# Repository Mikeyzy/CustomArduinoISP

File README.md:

# CustomArduinoISP
Custom ArduinoISP Board with Voltage Selection

This is a custom designed ArduinoISP based AVR ISP board, with 5V/3V3 selection switch and pwoer dilivery switch, you need ArduinoISP software which is avaliable in Examples from Arduino IDE, you can download it from www.arduino.cc

you need Autodesk EAGLE to open the schematics.

the license only apply to the hardware design, since the software is not included.

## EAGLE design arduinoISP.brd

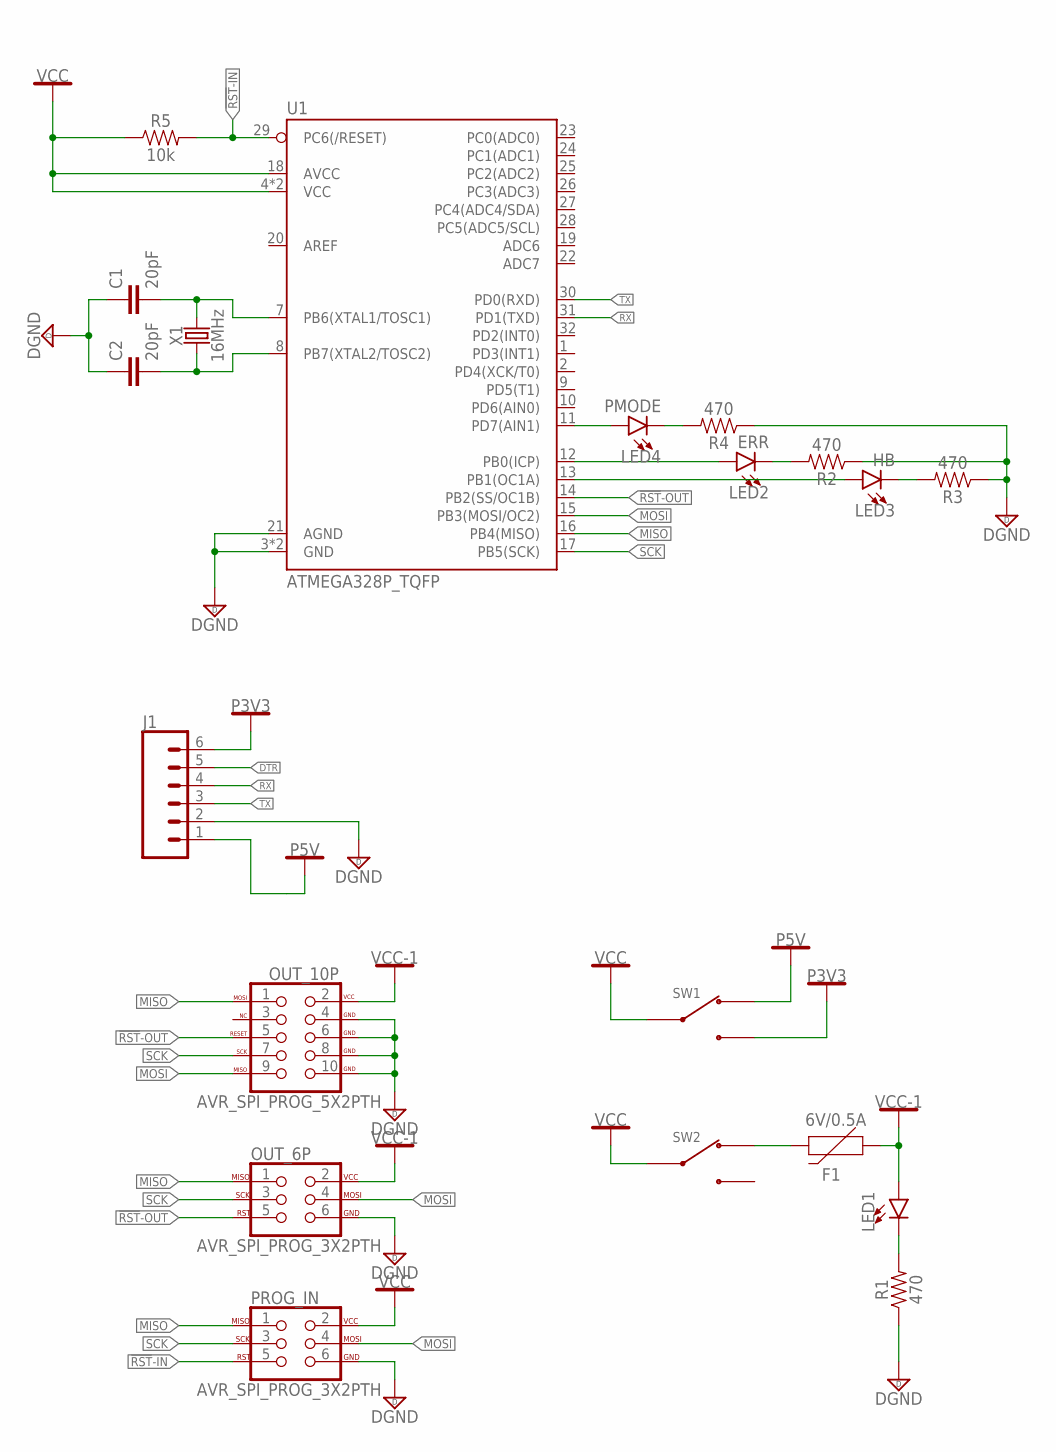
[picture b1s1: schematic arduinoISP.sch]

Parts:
C1, C2: 20pF; 0603
F1: 6V/0.5A; 1206
J1: CONN_06NO_SILK_NO_POP; 1X06_NO_SILK
LED1: LED3MM; LED_3MM
LED2: ERR; LED_3MM
LED3: HB; LED_3MM
LED4: PMODE; LED_3MM
OUT_6P: AVR_SPI_PROG_3X2PTH; 2X3
OUT_10P: AVR_SPI_PROG_5X2PTH; 2X5
PROG_IN: AVR_SPI_PROG_3X2PTH; 2X3
R1, R2, R3, R4: 470; 0603
R5: 10k; 0603
SW1, SW2: SW-SPDT_SS-12D02-VG4; SW_SS-12D10L5_FP
U1: ATMEGA328P_TQFP; TQFP32-08
X1: 16MHz; HC49US

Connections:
!RST!-IN: PROG_IN.5, R5.2, U1.29 (PC6(/RESET))
!RST!-OUT: OUT_6P.5, OUT_10P.5 (RESET), U1.14 (PB2(SS/OC1B))
DGND: C1.1, C2.1, J1.2, OUT_6P.6, OUT_10P.4 (GND), OUT_10P.6 (GND), OUT_10P.8 (GND), OUT_10P.10 (GND), PROG_IN.6, R1.1, R2.1, R3.1, R4.1, U1.3 (GND), U1.5 (GND), U1.21 (AGND)
DTR: J1.5
MISO: OUT_6P.1, OUT_10P.1 (MOSI), PROG_IN.1, U1.16 (PB4(MISO))
MOSI: OUT_6P.4, OUT_10P.9 (MISO), PROG_IN.4, U1.15 (PB3(MOSI/OC2))
unnamed: LED1.K (C), R1.2
unnamed: LED2.K (C), R2.2
unnamed: LED2.A, U1.12 (PB0(ICP))
unnamed: LED3.K (C), R3.2
unnamed: LED4.K (C), R4.2
unnamed: LED3.A, U1.13 (PB1(OC1A))
unnamed: LED4.A, U1.11 (PD7(AIN1))
unnamed: C1.2, U1.7 (PB6(XTAL1/TOSC1)), X1.2
unnamed: C2.2, U1.8 (PB7(XTAL2/TOSC2)), X1.1
unnamed: F1.2, SW2.P$1 (A)
P3V3: J1.6, SW1.P$3 (B)
P5V: J1.1, SW1.P$1 (A)
RX: J1.4, U1.31 (PD1(TXD))
SCK: OUT_6P.3, OUT_10P.7 (SCK), PROG_IN.3, U1.17 (PB5(SCK))
TX: J1.3, U1.30 (PD0(RXD))
VCC: PROG_IN.2, R5.1, SW1.P$2 (COM), SW2.P$2 (COM), U1.4 (VCC), U1.6 (VCC), U1.18 (AVCC)
VCC1: F1.1, LED1.A, OUT_6P.2, OUT_10P.2 (VCC)

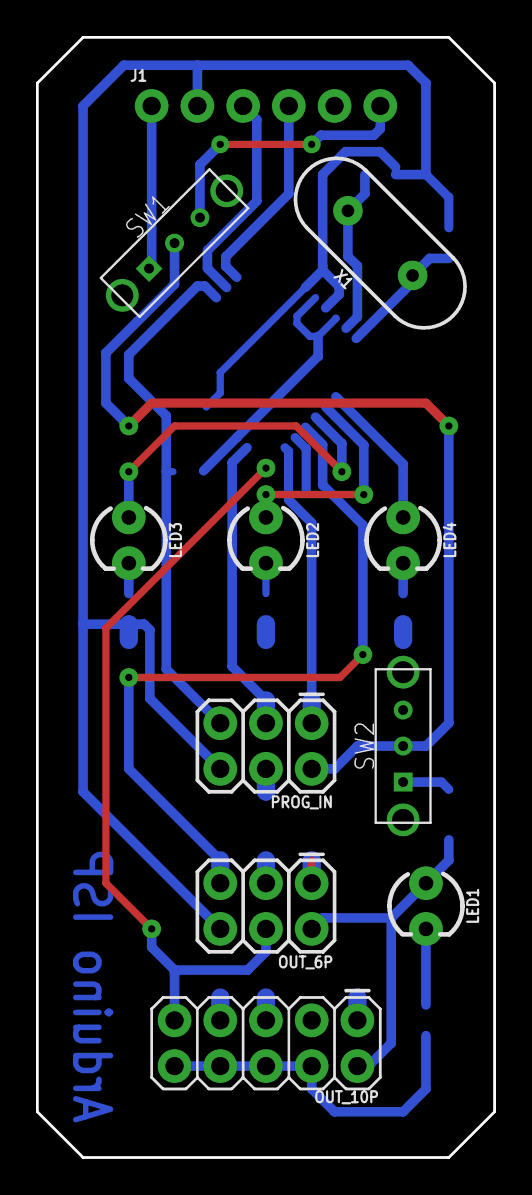
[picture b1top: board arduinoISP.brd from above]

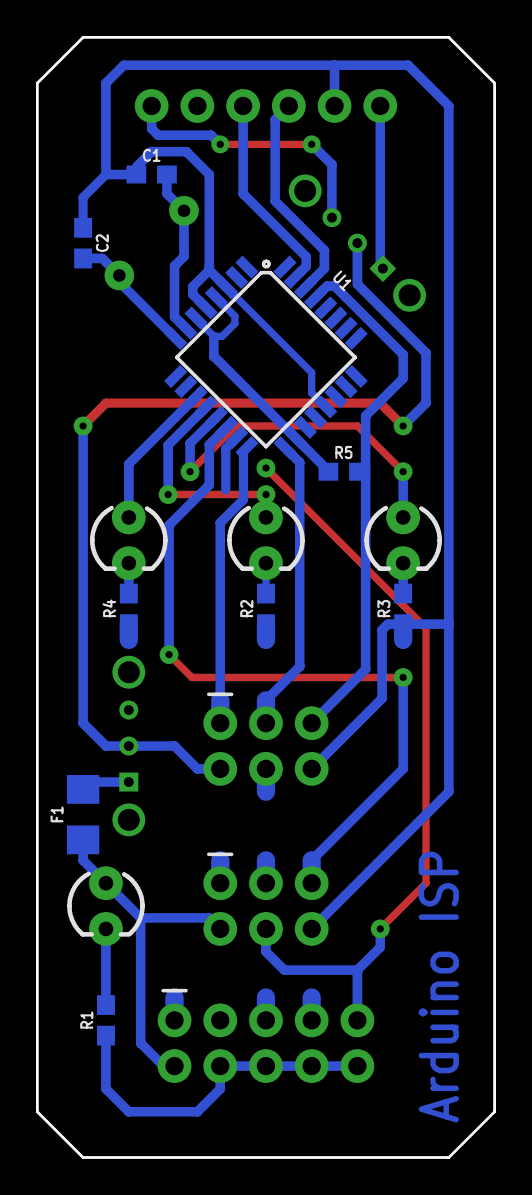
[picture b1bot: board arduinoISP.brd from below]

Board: 2 copper layers, 25.4 x 62.2 mm, 20 parts (9 on the bottom side), 22 nets.

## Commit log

2020-06-14 Add files via upload
    the single-sided PCB option, double-sided is comming soon.
2020-06-14 Rename arduinoISP.brd to single-side/arduinoISP.brd
2020-06-14 Rename arduinoISP.sch to single-side/arduinoISP.sch

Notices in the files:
parts and their libraries:
SparkFun-Fuses: Licensing: Creative Commons ShareAlike 4.0 International - https://creativecommons.org/licenses/by-sa/4.0
